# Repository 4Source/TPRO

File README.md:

# TPRO Light-Wall

## Contributing
- Each developer should checkout his ```feature Branch``` from the ```dev Branch``` !
- After clone: ```git checkout dev && git checkout -b myfeature```
- Merge Requests have to be made for destination ```dev```
#### Naming Feature Branches:
- ```<issue_number>-<feature/bug>-<decription>```
#### Naming Folders/Files:
- Structure inside Software Folder: ```src/my_layer/my_code.cpp```
- Structure in other Folders and Files (Dokumente): ```Documents/Sequence_Diagrams/Diagram_Day_Night.png```

Pay attention to capitalization and underscores outside of code Folders!

## Getting started

To make it easy for you to get started with GitLab, here's a list of recommended next steps.

Already a pro? Just edit this README.md and make it your own. Want to make it easy? [Use the template at the bottom](#editing-this-readme)!

## Add your files

* [Create](https://docs.gitlab.com/user/project/repository/web_editor/#create-a-file) or [upload](https://docs.gitlab.com/user/project/repository/web_editor/#upload-a-file) files
* [Add files using the command line](https://docs.gitlab.com/topics/git/add_files/#add-files-to-a-git-repository) or push an existing Git repository with the following command:

```
cd existing_repo
git remote add origin https://gitlab.com/immersight/research/tpro-light-wall.git
git branch -M main
git push -uf origin main
```

## Integrate with your tools

* [Set up project integrations](https://gitlab.com/immersight/research/tpro-light-wall/-/settings/integrations)

## Collaborate with your team

* [Invite team members and collaborators](https://docs.gitlab.com/user/project/members/)
* [Create a new merge request](https://docs.gitlab.com/user/project/merge_requests/creating_merge_requests/)
* [Automatically close issues from merge requests](https://docs.gitlab.com/user/project/issues/managing_issues/#closing-issues-automatically)
* [Enable merge request approvals](https://docs.gitlab.com/user/project/merge_requests/approvals/)
* [Set auto-merge](https://docs.gitlab.com/user/project/merge_requests/auto_merge/)

## Test and Deploy

Use the built-in continuous integration in GitLab.

* [Get started with GitLab CI/CD](https://docs.gitlab.com/ci/quick_start/)
* [Analyze your code for known vulnerabilities with Static Application Security Testing (SAST)](https://docs.gitlab.com/user/application_security/sast/)
* [Deploy to Kubernetes, Amazon EC2, or Amazon ECS using Auto Deploy](https://docs.gitlab.com/topics/autodevops/requirements/)
* [Use pull-based deployments for improved Kubernetes management](https://docs.gitlab.com/user/clusters/agent/)
* [Set up protected environments](https://docs.gitlab.com/ci/environments/protected_environments/)

***

# Editing this README

When you're ready to make this README your own, just edit this file and use the handy template below (or feel free to structure it however you want - this is just a starting point!). Thanks to [makeareadme.com](https://www.makeareadme.com/) for this template.

## Suggestions for a good README

Every project is different, so consider which of these sections apply to yours. The sections used in the template are suggestions for most open source projects. Also keep in mind that while a README can be too long and detailed, too long is better than too short. If you think your README is too long, consider utilizing another form of documentation rather than cutting out information.

## Name
Choose a self-explaining name for your project.

## Description
Let people know what your project can do specifically. Provide context and add a link to any reference visitors might be unfamiliar with. A list of Features or a Background subsection can also be added here. If there are alternatives to your project, this is a good place to list differentiating factors.

## Badges
On some READMEs, you may see small images that convey metadata, such as whether or not all the tests are passing for the project. You can use Shields to add some to your README. Many services also have instructions for adding a badge.

## Visuals
Depending on what you are making, it can be a good idea to include screenshots or even a video (you'll frequently see GIFs rather than actual videos). Tools like ttygif can help, but check out Asciinema for a more sophisticated method.

## Installation
Within a particular ecosystem, there may be a common way of installing things, such as using Yarn, NuGet, or Homebrew. However, consider the possibility that whoever is reading your README is a novice and would like more guidance. Listing specific steps helps remove ambiguity and gets people to using your project as quickly as possible. If it only runs in a specific context like a particular programming language version or operating system or has dependencies that have to be installed manually, also add a Requirements subsection.

## Usage
Use examples liberally, and show the expected output if you can. It's helpful to have inline the smallest example of usage that you can demonstrate, while providing links to more sophisticated examples if they are too long to reasonably include in the README.

## Support
Tell people where they can go to for help. It can be any combination of an issue tracker, a chat room, an email address, etc.

## Roadmap
If you have ideas for releases in the future, it is a good idea to list them in the README.

## Contributing
State if you are open to contributions and what your requirements are for accepting them.

For people who want to make changes to your project, it's helpful to have some documentation on how to get started. Perhaps there is a script that they should run or some environment variables that they need to set. Make these steps explicit. These instructions could also be useful to your future self.

You can also document commands to lint the code or run tests. These steps help to ensure high code quality and reduce the likelihood that the changes inadvertently break something. Having instructions for running tests is especially helpful if it requires external setup, such as starting a Selenium server for testing in a browser.

## Authors and acknowledgment
Show your appreciation to those who have contributed to the project.

## License
For open source projects, say how it is licensed.

## Project status
If you have run out of energy or time for your project, put a note at the top of the README saying that development has slowed down or stopped completely. Someone may choose to fork your project or volunteer to step in as a maintainer or owner, allowing your project to keep going. You can also make an explicit request for maintainers.

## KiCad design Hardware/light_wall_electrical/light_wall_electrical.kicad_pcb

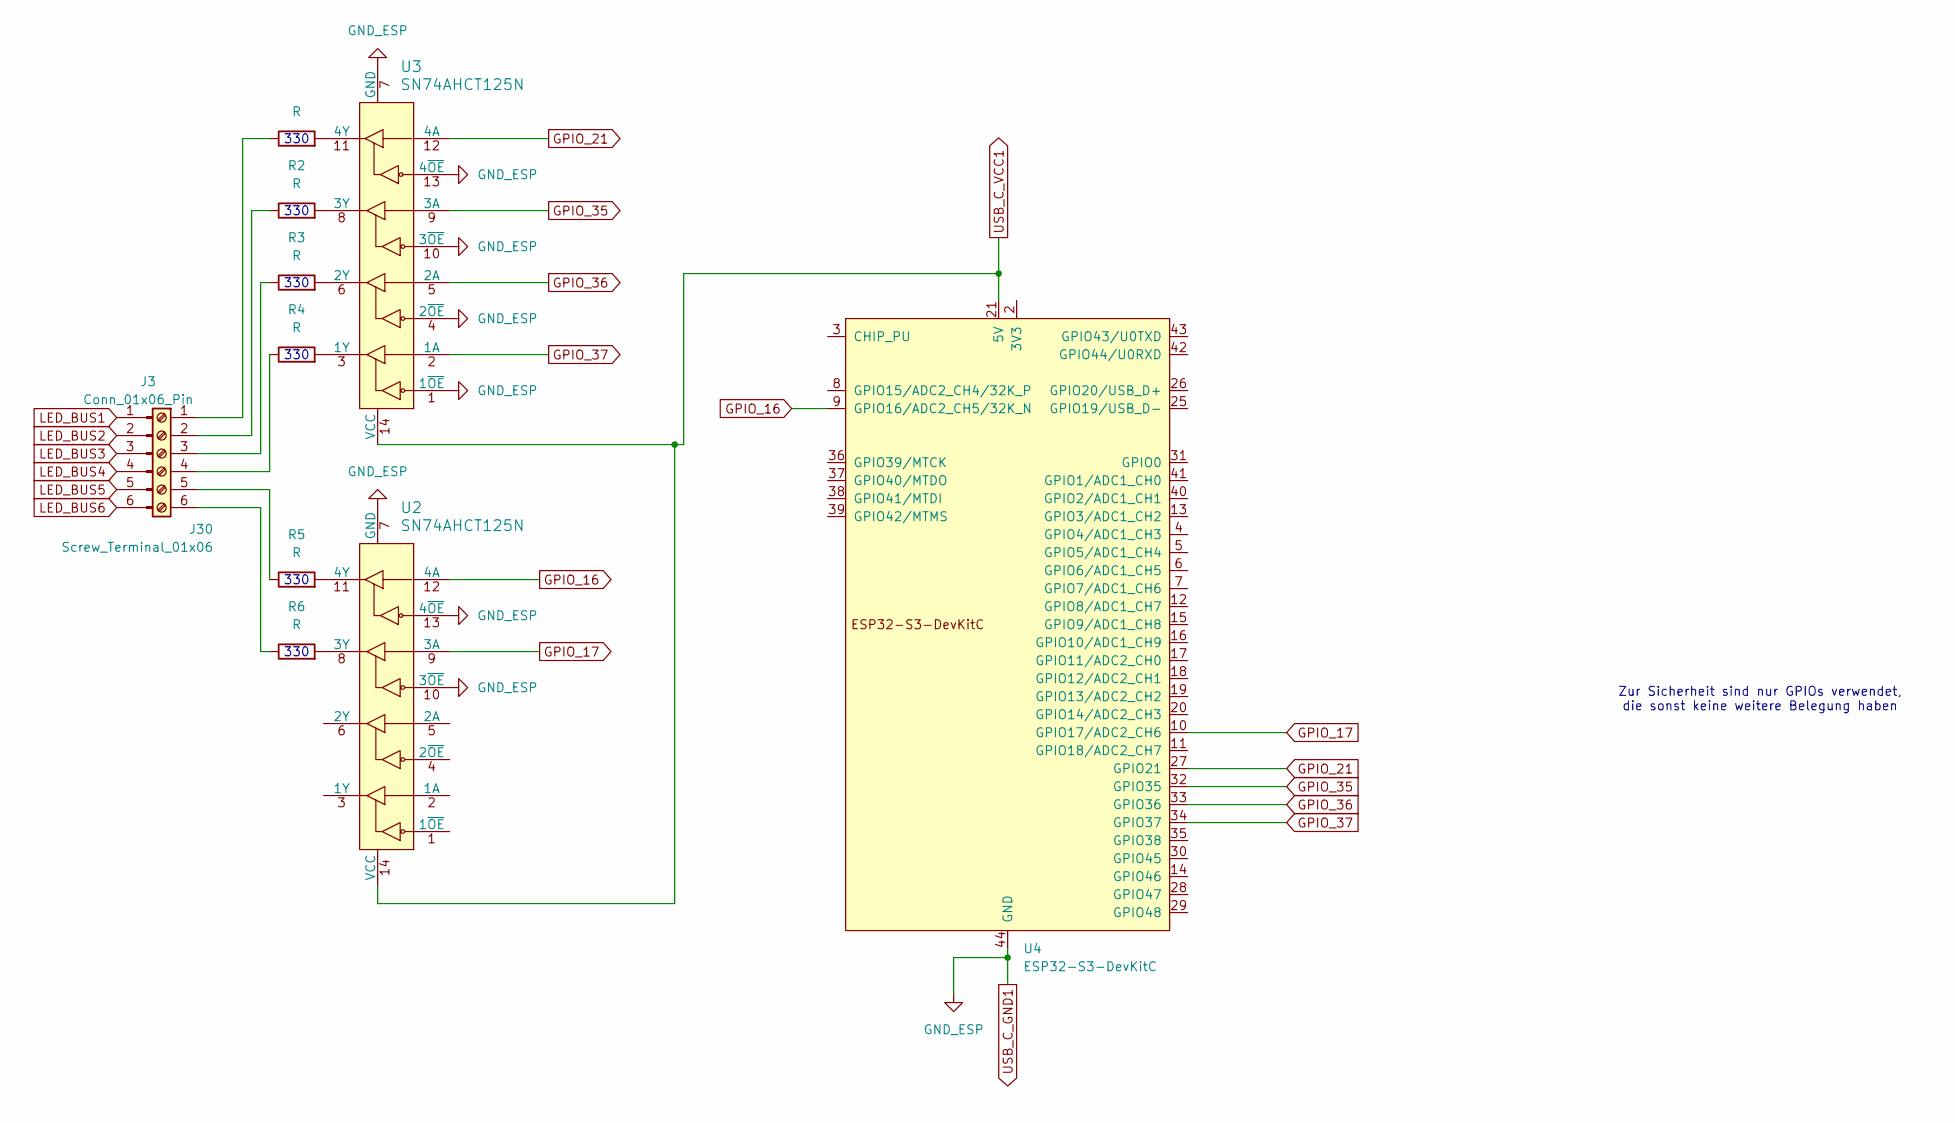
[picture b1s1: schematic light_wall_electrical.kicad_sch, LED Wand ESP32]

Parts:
J3: Conn_01x06_Pin; PinHeader_1x06_P2.54mm_Horizontal
J30: Screw_Terminal_01x06; TerminalBlock_Phoenix_MKDS-1,5-6-5.08_1x06_P5.08mm_Horizont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
R1, R2, R3, R4, R5, R6: R; R_Axial_DIN0207_L6.3mm_D2.5mm_P7.62mm_Horizontal
U2, U3: SN74AHCT125N; DIP-14_W7.62mm; MPN SN74AHCT125N; Digi-Key_PN 296-4655-5-ND
U4: ESP32-S3-DevKitC

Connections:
GPIO_16: U2.12 (4A), U4.9 (GPIO16/ADC2_CH5/32K_N)
GPIO_17: U2.9 (3A), U4.10 (GPIO17/ADC2_CH6)
GPIO_21: U3.12 (4A), U4.27 (GPIO21)
GPIO_35: U3.9 (3A), U4.32 (GPIO35)
GPIO_36: U3.5 (2A), U4.33 (GPIO36)
GPIO_37: U3.2 (1A), U4.34 (GPIO37)
LED_GND_1: U2.7 (GND), U2.10 (3~OE), U2.13 (4~OE), U3.1 (1~OE), U3.4 (2~OE), U3.7 (GND), U3.10 (3~OE), U3.13 (4~OE), U4.22 (GND), U4.23 (GND), U4.24 (GND), U4.44 (GND)
unnamed: J30.1, R1.1
unnamed: J30.2, R2.1
unnamed: J30.3, R3.1
unnamed: J30.4, R4.1
unnamed: J30.5, R5.1
unnamed: J30.6, R6.1
unnamed: R6.2, U2.8 (3Y)
unnamed: R5.2, U2.11 (4Y)
unnamed: R4.2, U3.3 (1Y)
unnamed: R3.2, U3.6 (2Y)
unnamed: R2.2, U3.8 (3Y)
unnamed: R1.2, U3.11 (4Y)
unnamed: U4.1 (3V3), U4.2 (3V3)
USB_C_VCC1: U2.14 (VCC), U3.14 (VCC), U4.21 (5V)

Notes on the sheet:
330
Zur Sicherheit sind nur GPIOs verwendet, die sonst keine weitere Belegung haben

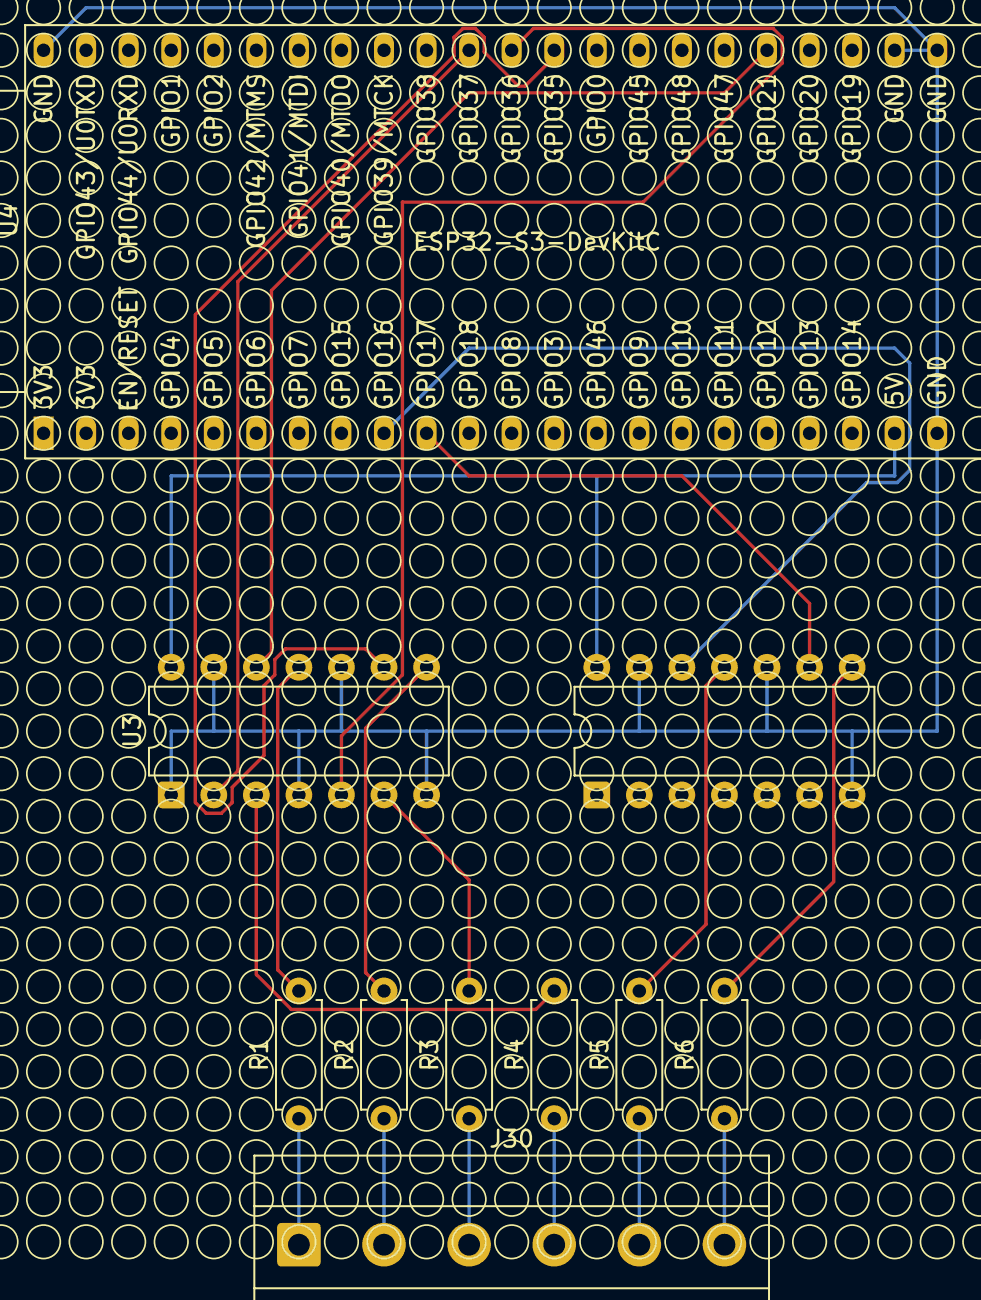
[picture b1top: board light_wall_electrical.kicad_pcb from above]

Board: 2 copper layers, 10 parts (0 on the bottom side), 21 nets.

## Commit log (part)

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2026-03-22 Add Basic Templates
2026-03-22 Add Complexity input to Task
2026-03-26 Added blink and setup manual
2026-03-26 Added esp-clang to PATH
2026-04-08 Main is now the development branch
2026-04-08 Hotfix component dependencies
2026-04-08 66 feature files
    !9 should be merged first
    -- Commits included: --
    * Added JSON Config Export
    * Improve Full clean to remove all files mentioned in a .gitignore
    * Add package-lock.json to .gitignore
    * Ensure npm dependencies are installed when running task
2026-04-08 68 feature implement mapping
    -- Commits included: --
    * Improve Full clean to remove all files mentioned in a .gitignore
    * Add package-lock.json to .gitignore
    * Ensure npm dependencies are installed when running task
    * Use svg instead of png
    * Lix linting of web files
2026-04-08 [FEAT] 73 feature setup ci
    <!--In the title above, provide a meaningful summary with [FIX] for bug fix and [FEAT] for new feature --->
    ## Describe your changes
    <!--Describe your changes in detail --->
    * Added gitlab runner
    * Pytest on esp
    * build preact and idf
2026-04-08 -- Commits included: -- * Modified default MR template
    * Added default MR template
2026-04-08 -- Commits included: -- * Start pipeline from web
2026-04-10 -- Commits included: -- * Fixed duplicate
    * Run CI only when MR to main or push to main and Changes in Software/
    * Fixed clang-format errors
    * Fixed clang-tidy Errors
    * clang-tidy fix - clang-format test
    * run clang-tidy script from ci
    * Added tidy script and task
2026-04-10 -- Commits included: -- * Add sequence diagrams for Day/Night and Timeline effect loading
2026-04-10 -- Commits included: -- * Revert separated npm install because not working
    * Fix missing path switch for npm install
    * Add missing rules for npm install
    * Separate npm dependencies install + Fixed test linting error
    * Add test linting error
    * Add missing install before linting
    * Add lint check for website
2026-04-10 -- Commits included: -- * Update README.md to update dependency instructions
    * Remove empty/unused component output_layer
    * Add idf_component.yml files to the components
2026-04-10 -- Commits included: -- * Hotfix made clang-tidy output more visual
2026-04-10 -- Commits included: -- * Update observer notification, add, remove logic in ConfigManager and LightEffectManager
    * Fix missing dependency
    * Refactor: integrate LightEffectManager as ConfigObserver, remove legacy ILedFrameSink interface, change ConfigManager's add_observer logic
    * Add BlinkingEffect implementation for the Simulation Website Test
2026-04-13 -- Commits included: -- * Only notify websocket when data realy changes
    * Added mocks for task handle give/take
    * Added TaskHandles
    * Setup custom partitiontable for 16MB flashsize
    * create unittest build dir in ci
    * Fix clang-format errors
    * Fix weblinting errors
2026-04-14 -- Commits included: -- * Added span views of servers
    * added more functions and another timeserver
    * Fix clang-tidy
    * Extend timeserver functionality with configuration options for polling interval and timezone
    * shortened polling time
    * clang format, added comments
    * fixed errors, clang format
2026-04-14 -- Commits included: -- * Fix format
    * Change default config to ethernet
    * Clang Tidy fixes + code documentation
    * Add option to ignore macros in cognitive complexity checks
    * Implement Ethernet connection
    * Change Ethernet and Wi-Fi connection management
    - Added EthernetNetwork and WifiNetwork classes for handling respective connections.
2026-04-15 -- Commits included: -- * clang tidy
    * added mdns to both ethernet and wifi
2026-04-15 -- Commits included: -- * .gitlab-ci.yml set timeout to 10m
    * USB Port timeout 5m - run clang-tidy on multiple cores
    * Initialize path_buffer
    * Fix clang-tidy
    * Added effect factory unittest
    * switch to std::string for filepaths
    * Added timeline effect
2026-04-15 -- Commits included: -- * Fix unittest
    * Fix ws server sending the wrong data
    * Refactor time component and add DateTime class with unit tests
    * Create tmp frames on Heap
    * start blink effect
    * create unittest build dir in ci
    * Fix weblinting errors
2026-04-16 -- Commits included: -- * keep rvalue and use std::forward to fix clang-tidy
    * Update build-job-idf to depend on generate-certificate
    * Include header in Clang-Tidy checks + Fixing them
    * Update webserver to support both HTTP and HTTPS, HTTP used to automatically redirect to HTTPS
    * Update webserver to support HTTPS by replacing HTTP server references and adding event handling for HTTPS events
    * Refactor webserver implementation to use a class structure and improve event handling
    * Add unit tests task to VSCode configuration
2026-04-16 -- Commits included: -- * Fix print
    * Changed filemanager to use SPI3 for sd card
    * Fix clang-tidy
    * run clang-format
    * refactor: migrate file_manager to use SPI interface and remove native unit tests
    * • Implement the FileManager component with methods to mount/unmount the card + save, read, delete and list the files
    • Implement additional unit tests and pytest support to check the workflow
2026-04-17 -- Commits included: -- * Fix sdkconfig path handling in certificate generation script
    * Refactor mDNS hostname to use CONFIG_LWIP_LOCAL_HOSTNAME and update certificate generation script to also use CONFIG_LWIP_LOCAL_HOSTNAME and localhost for generation
2026-04-19 -- Commits included: -- * changed if else to switch case and moved restserver to webserver component
    * clang format
    * included header array
    * clang tidy
    * fixed build, really this time
    * fixed build error
    * completed basic rest api for configurations
2026-04-19 -- Commits included: -- * Enhance network handling and logging capabilities
    - Updated polling interval for timeserver to 10800000 ms (3h)
    - Increased SPI clock speed to 40 MHz for Ethernet initialization.
    - Added debug logging for Ethernet and WiFi initialization and connection processes.
    - Refactored webserver to include detailed logging for active socket connections and various server events.
    - Introduced new methods for handling HTTP and HTTPS server events.
    - Configured maximum socket connections to 11 in sdkconfig.defaults.
2026-04-20 -- Commits included: -- * Fix pipeline
    * Enhance ConfigManager and RestServer error handling and logging
    - Fix crash on unknown query parameter to Rest API
    - Fix missing responses on error
    * Fix large file download
    * Implement fileserver frontend
    * Add fileserver functionality
2026-04-20 -- Commits included: -- * Fix tidy & unittests
    * Make use of FileManager
    * Added prints
    * Added default_configs - write them to sdcard in main
    * No check size of subeffects array
    * Initialize subeffects and set overwrites
    * Setup unit test debugging
2026-04-20 -- Commits included: -- * Added Titles to pdf
    * Added kicad shematics
2026-04-26 -- Commits included: -- * Add .gitignore and remove backup files
    - Created a .gitignore file to exclude backup files and history from tracking.
    - Deleted multiple backup zip files from the light_wall_electrical directory.
    - Removed the .history file that tracked subproject commits.
    * Added empty lines before comments
    * Ignore unused variable Errors
    * Fixed Web Linting Errors
2026-04-29 -- Commits included: -- * Setup Debugger
2026-04-29 -- Commits included: -- * clang format
    * mdns service is now stopped, when diconnecting from ethernet or wifi
2026-04-29 -- Commits included: -- * Clang format fixes
    * Clang Tidy fixes
    * feat: implement JSON-based configuration serialization and persistence in ConfigManager
2026-04-29 -- Commits included: -- * mdns is freed after ip is lost
2026-04-29 -- Commits included: -- * Resolved threads
    * Fix pytest
    * Fixed Unittests
    * Fix build and certificate generation
    * task.json set commands to build led_wall_master app
    * Clang_tidy for multiple apps
    * Added sdkconfig.defaults for other apps
2026-05-07 -- Commits included: -- * Clang tidy fixes
    * Fix day night
    * Fix Heap allocation
    * Use ArduinoJson for continent effect
    * Fix continent effect
    * Fix timeline
    * Adaptions
2026-05-07 -- Commits included: -- * Fix x/y order
    * Add sun data generation functionality to SettingsMenu and create sunapi module
2026-05-08 -- Commits included: -- * Make Parameter settings available
    * Effects start properly now when using UI
    * Make new effects available
    * Rebased on branch 137-feature-new-basic-effects
    * New: Save Effects, Change Dot Size, Select On time
    * More Changes
    * Changes to UI
2026-05-08 -- Commits included: -- * Interrupt Effect in Timeline & added LOGD for all prints
    * Fixed clang-tidy
    * Add fast forward effect
2026-05-09 -- Commits included: -- * Added SunData
    * Fixes
    * Fix effect management and enhance config logging
    * Fix format
    * Fix isDurringWorkingHours
    * Fix config manager
    * Add active time configuration support in ConfigManager and LightEffectManager
2026-05-10 Upload New File
2026-05-10 doc: add sun-data JSON files and the User Manual documentation
2026-05-10 add sun-data JSON files
2026-05-10 -- Commits included: -- * Add 03-04 Sun data
2026-05-10 Add Excalidraw Board
